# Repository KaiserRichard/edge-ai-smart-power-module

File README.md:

# Edge AI Smart Power Module — V1A-Lite

This branch (`feat/v1a-lite-cost-reduction`) captures **V1A-Lite option 1R**: 18–26 V normal auxiliary input (24 V nominal) → reverse protection and latched input cutoff → LM61460 → raw-node SCR crowbar → 7 A wiring fuse → Pi power output. The 100k/24.6k feedback divider sets 5.065 V nominal; 5 A operation remains a qualification target. Telemetry and the series shunt are removed.

**Phase D capture: ERC 0 errors / 0 warnings. Electrical release remains BLOCKED. NOT FOR FABRICATION — ENGINEERING REVIEW REQUIRED.** No Pi until dummy-load and OV/crowbar qualification gates pass.

Read the [Phase D capture and open items](docs/evidence/v1a_lite/PHASE_D_CAPTURE.md), [five-page schematic PDF](docs/schematic/V1A_Lite_schematic.pdf), [BOM](docs/evidence/v1a_lite/V1A_LITE_BOM.csv), and [progress/handoff](docs/evidence/v1a_lite/PHASE_D_PROGRESS.md). The schematic has root plus Sheets 01, 02, 03 and 05.

The old research design is preserved on **`v1a-research-schematic`** and **`v1a-research-layout-wip`**. The existing `V1A.kicad_pcb` is unchanged historical research layout, **not a V1A-Lite board**. Older context and architecture documents below describe research V1A unless explicitly identified as Lite; its 9–24 V/I2C architecture does not govern this branch. No final WBR battery or robot architecture is assumed.

## Start here

- [Current engineering state and blockers](docs/context/03_ENGINEERING_STATE.md)
- [Project overview](docs/context/01_PROJECT_OVERVIEW.md) and [current architecture](docs/context/02_V1A_ARCHITECTURE.md)
- [Workflow/gates](docs/context/05_WORKFLOW_AND_GATES.md), [decision index](docs/context/06_DECISION_LOG.md), and [learning sequence](docs/context/04_LEARNING_CURRICULUM.md)
- [Manager report](docs/FINAL_MANAGER_REPORT.md) and [detailed blocker evidence](docs/evidence/r2/forensic_2026-09-14/R2_R3_BLOCKER_REVIEW.md)
- [AI instructions](CLAUDE.md), [repository rules](AGENTS.md), and [Claude Project file selection](docs/CLAUDE_PROJECT_SETUP.md)

## Repository layout

| Path | Contents |
| --- | --- |
| `hardware/kicad/` | Lite root/four functional schematics and libraries; unchanged historical research PCB |
| `docs/context/` | Compact current project context; read before dated proposals |
| `docs/00_…05_*.md` | Requirements and design/review history; dated notices identify older state |
| `docs/evidence/` | Engineering provenance, calculations, contracts, source registers, dated netlists/ERC/review exports |
| `scripts/`, `tests/` | Calculation, capture, footprint, and repository checks |
| `software/power_monitor/` | Documented future telemetry work; no runtime implementation yet |
| `measurements/`, `fabrication/` | Documented future gated evidence/release areas |
| `third_party/` | Source registry, retained download manifest, small licensed historical reference extracts |

## Safe validation

From the repository root, with Python 3.11 or compatible Python 3:

```sh
python3 -B scripts/check_repository.py
python3 -B -m unittest discover -s tests -v
python3 -B scripts/check_v1a_lite.py
```

These commands check Lite capture integrity and retained historical regressions, not electrical release. The repository runner selects the Lite profile; incompatible research architecture suites are explicitly skipped. No software build is currently required. [Validation instructions](docs/VALIDATION.md) include fresh KiCad export/ERC commands, expected failure symptoms, and optional tools. Do not run the schematic builder as a check: it writes design files.

Vendor downloads, full predecessor repositories, backups, environments, and scratch renders were preserved in a sibling local archive. They are not restored by cloning GitHub. [Third-party policy/restoration](third_party/README.md) and the [cleanup record](docs/REPOSITORY_CLEANUP.md) explain dependencies and recovery. Historical engineering evidence remains in Git.

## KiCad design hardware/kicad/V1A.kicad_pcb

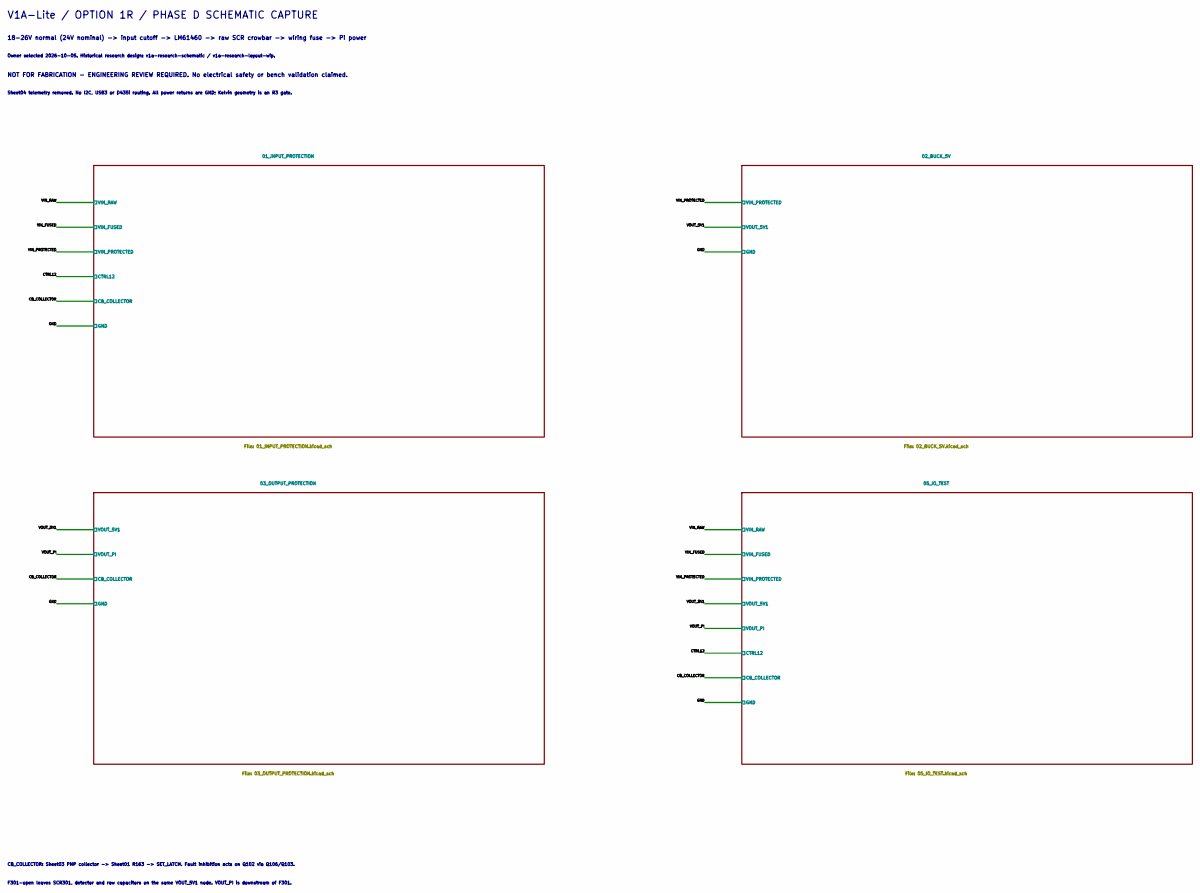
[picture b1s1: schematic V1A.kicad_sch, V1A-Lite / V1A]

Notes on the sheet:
V1A-Lite / OPTION 1R / PHASE D SCHEMATIC CAPTURE
18-26V normal (24V nominal) -> input cutoff -> LM61460 -> raw SCR crowbar -> wiring fuse -> Pi power
Owner selected 2026-10-05. Historical research design: v1a-research-schematic / v1a-research-layout-wip.
NOT FOR FABRICATION - ENGINEERING REVIEW REQUIRED. No electrical safety or bench validation claimed.
Sheet04 telemetry removed. No I2C, USB3 or D435i routing. All power returns are GND; Kelvin geometry is an R3 gate.
CB_COLLECTOR: Sheet03 PNP collector -> Sheet01 R163 -> SET_LATCH. Fault inhibition acts on Q102 via Q106/Q103.
F301-open leaves SCR301, detector and raw capacitors on the same VOUT_5V1 node. VOUT_PI is downstream of F301.

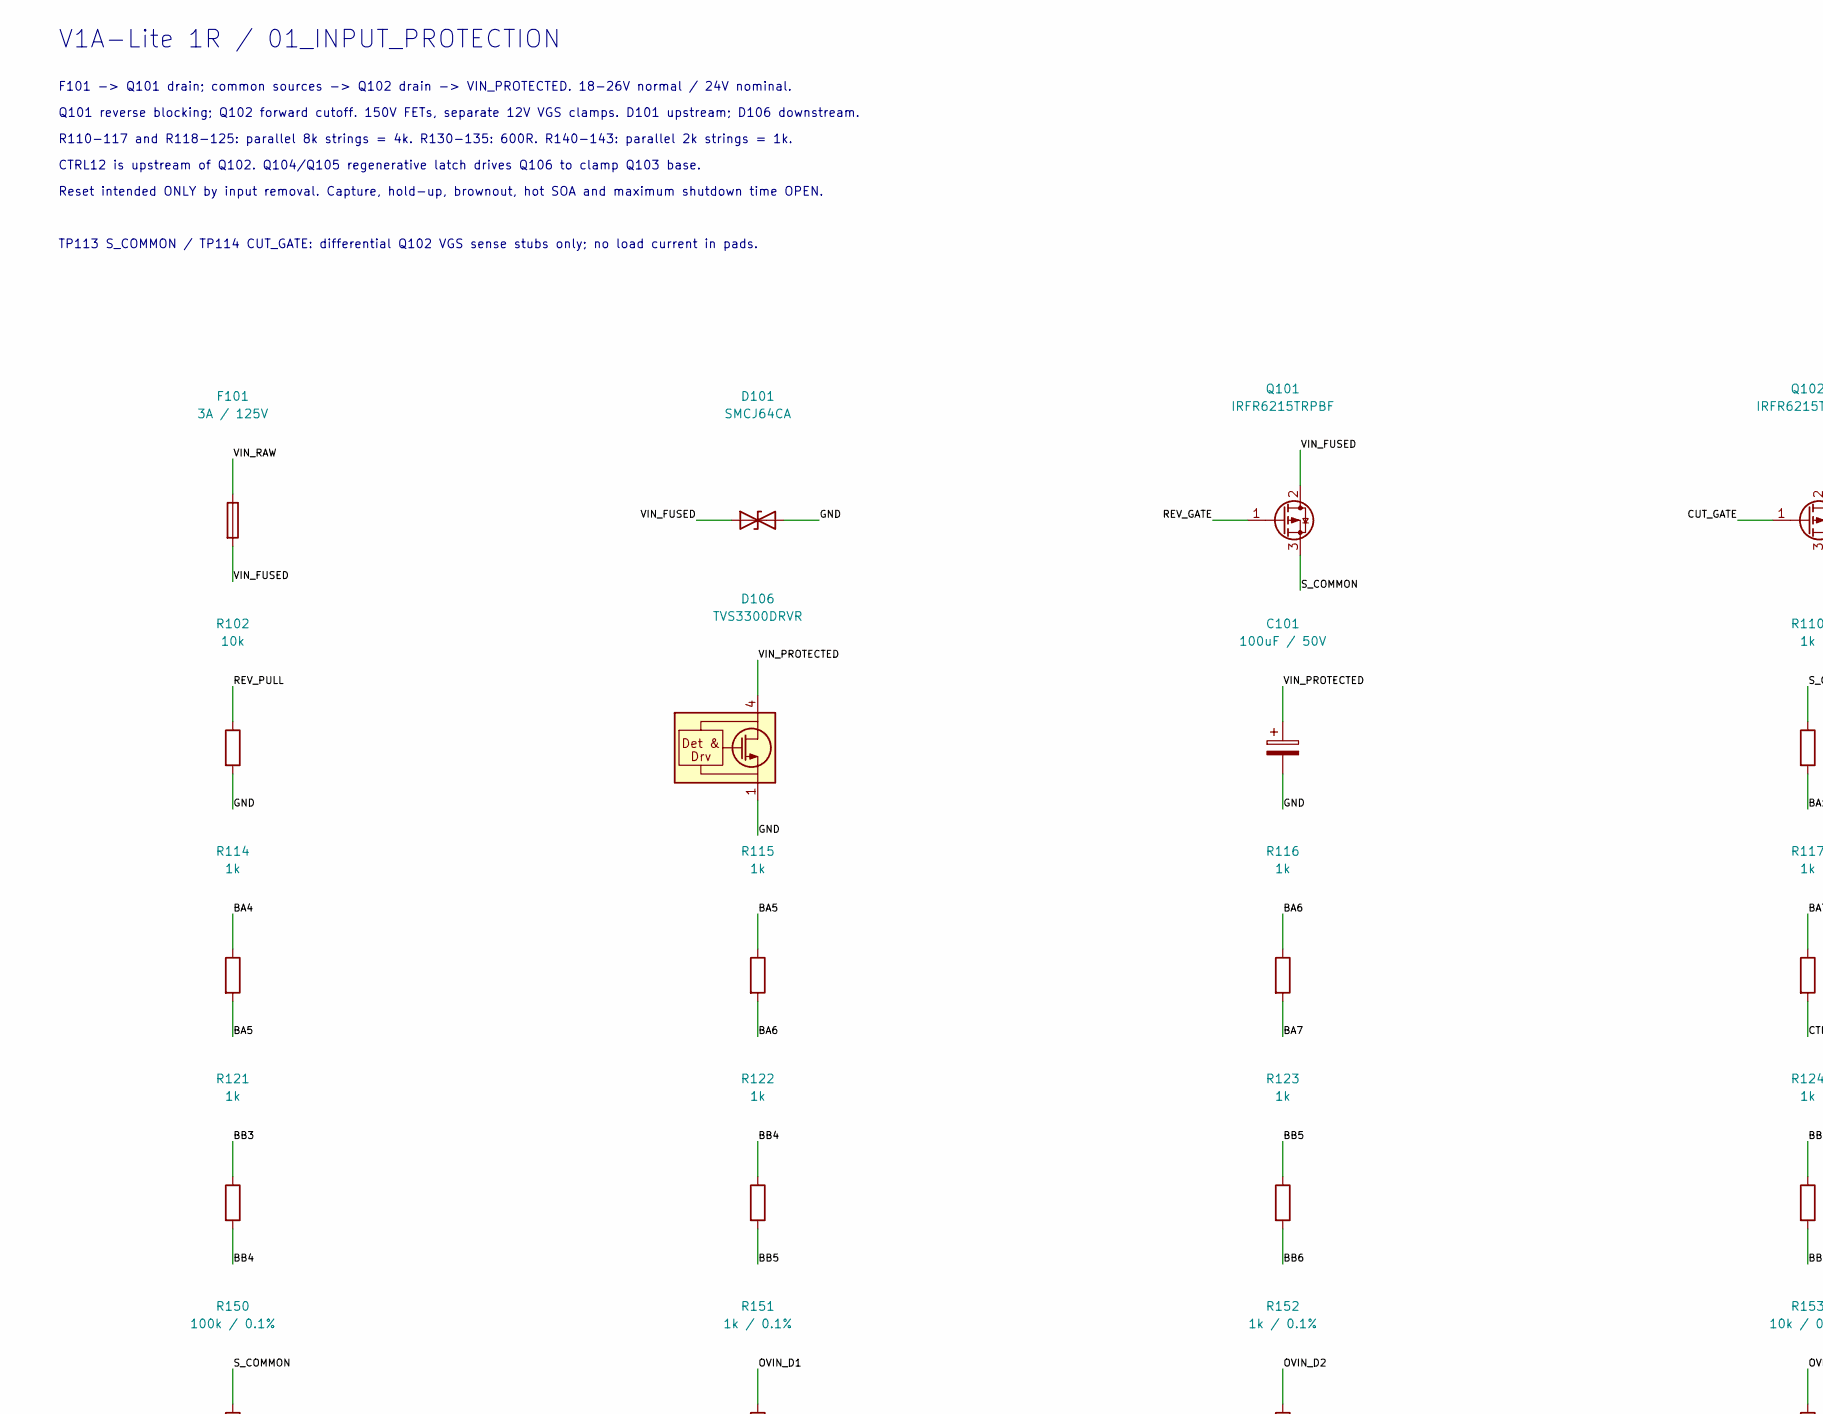
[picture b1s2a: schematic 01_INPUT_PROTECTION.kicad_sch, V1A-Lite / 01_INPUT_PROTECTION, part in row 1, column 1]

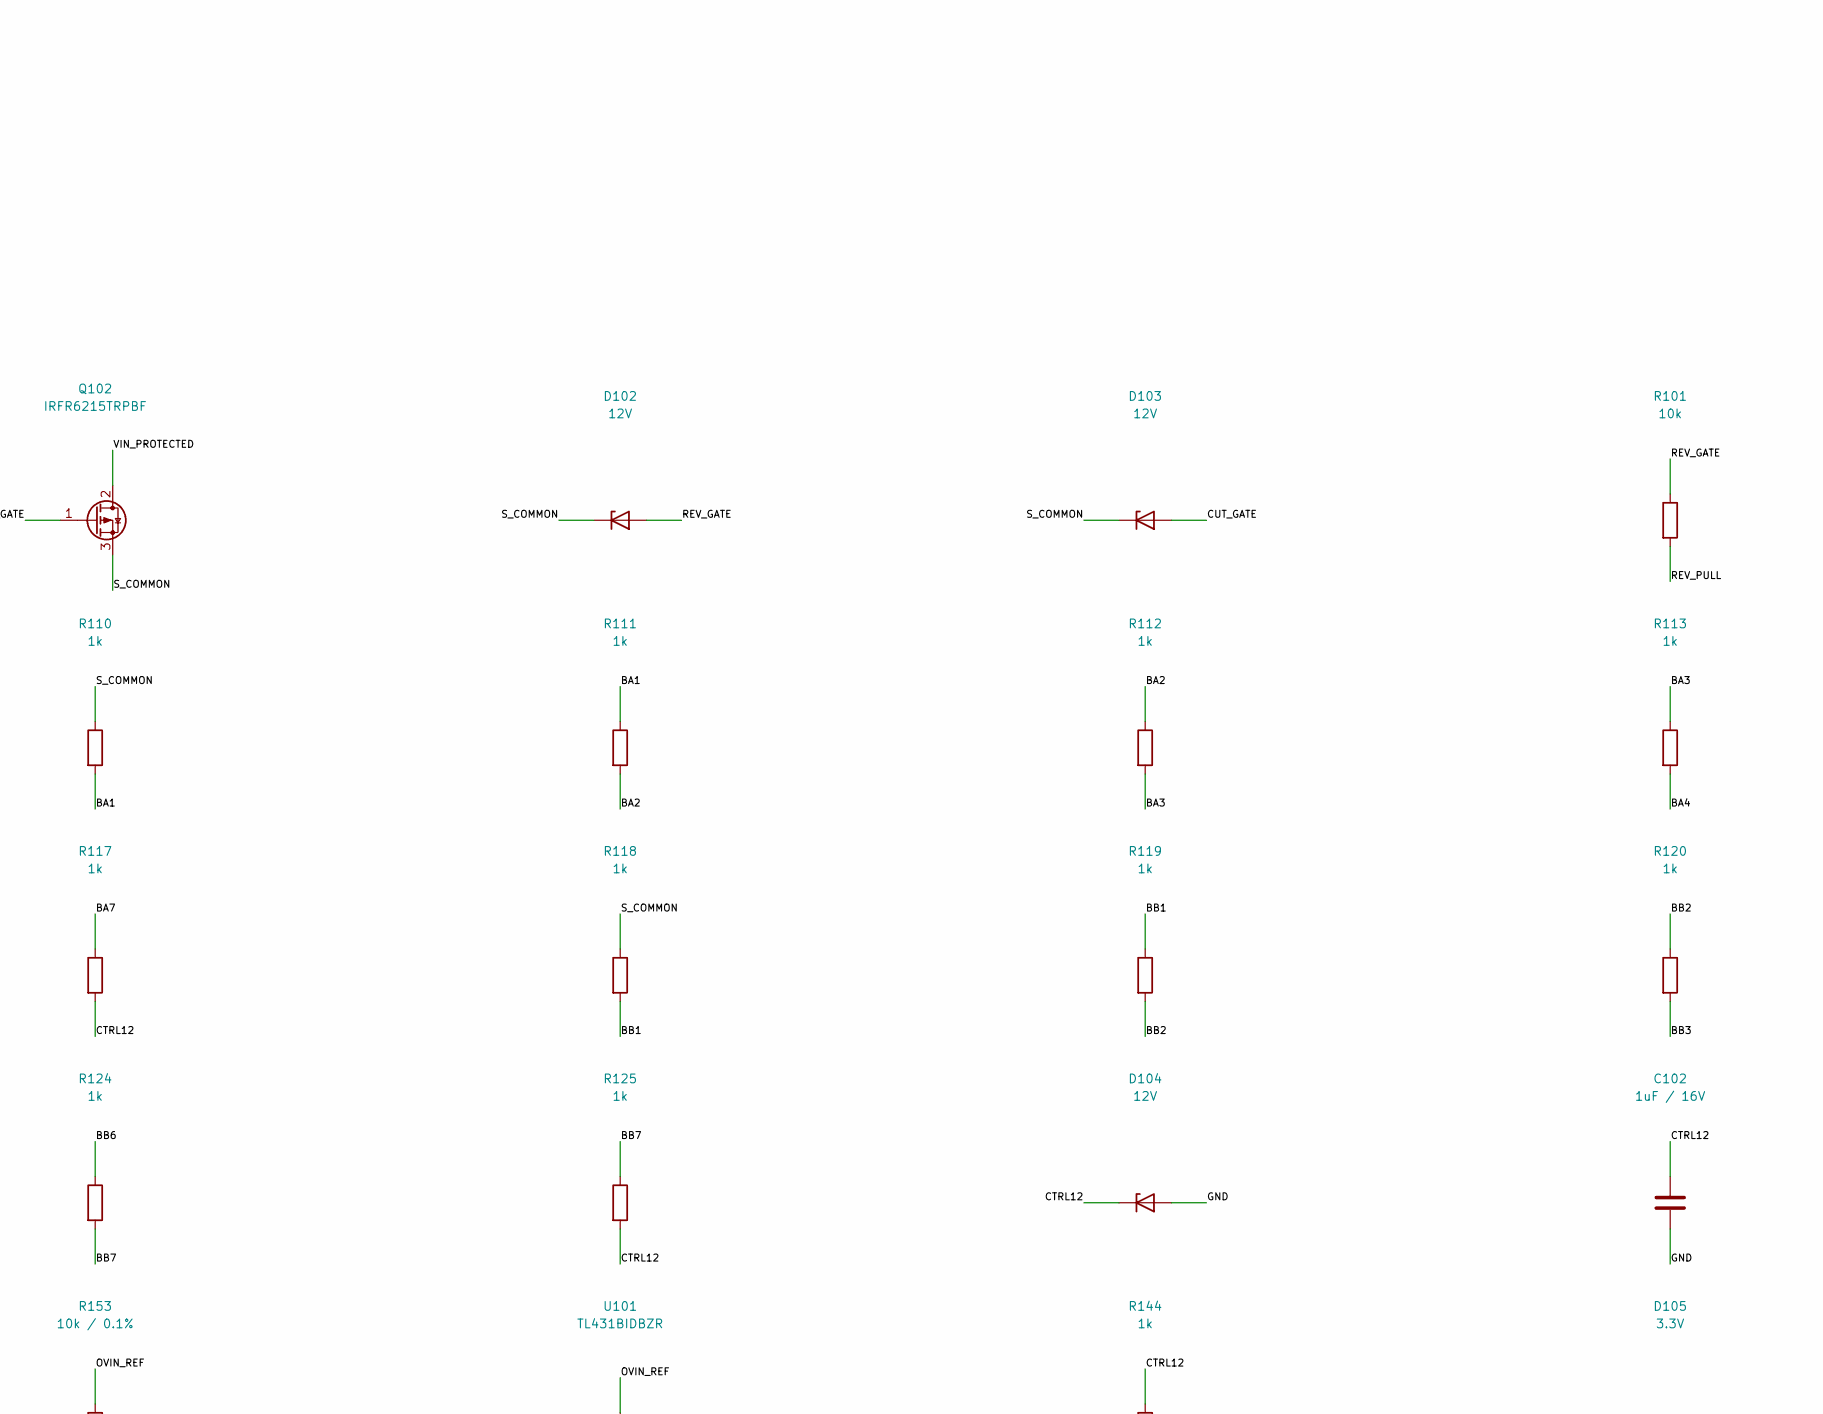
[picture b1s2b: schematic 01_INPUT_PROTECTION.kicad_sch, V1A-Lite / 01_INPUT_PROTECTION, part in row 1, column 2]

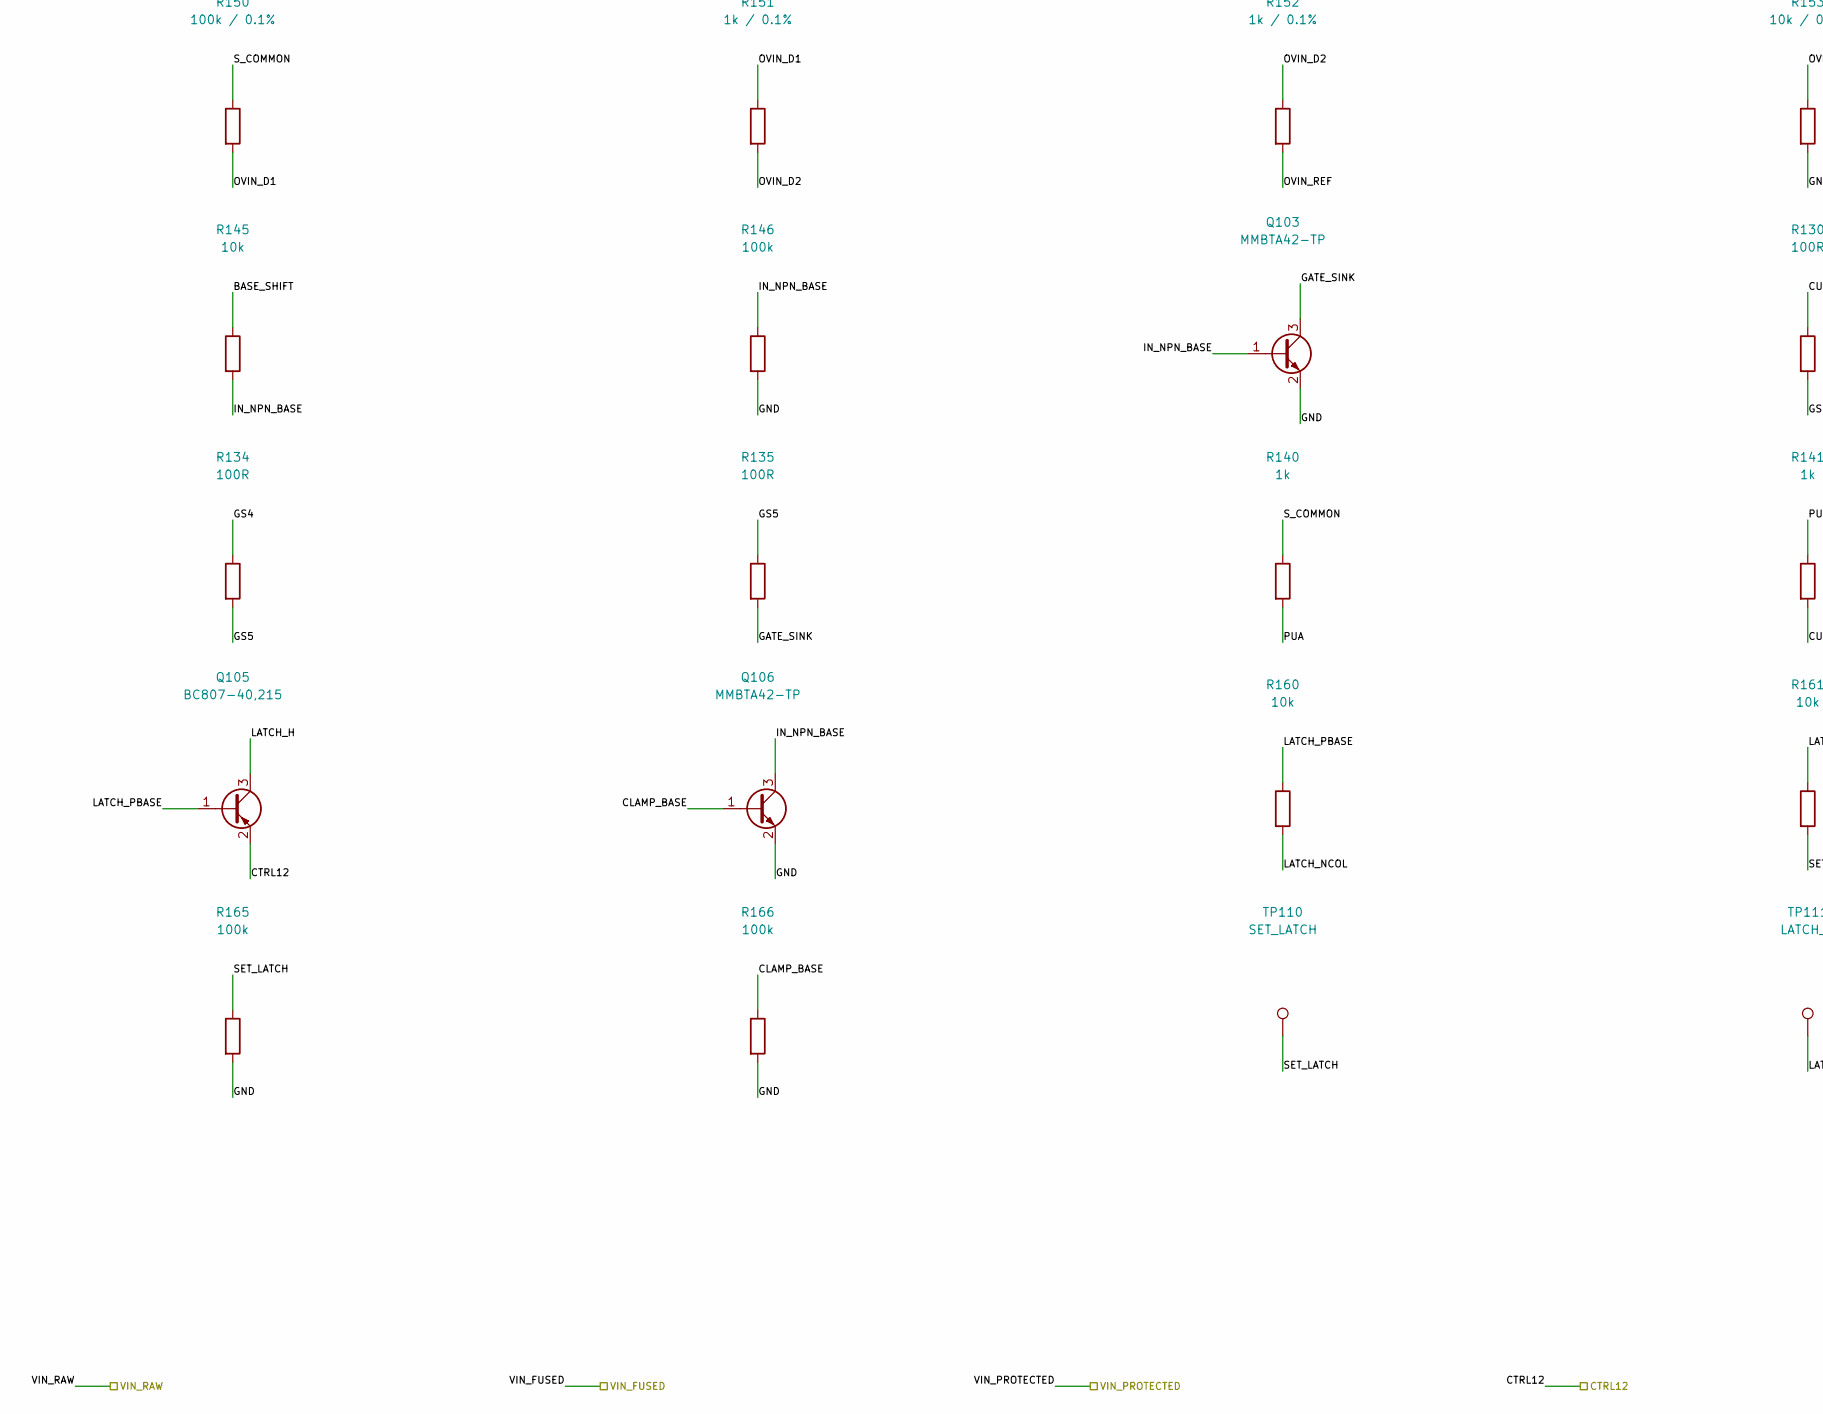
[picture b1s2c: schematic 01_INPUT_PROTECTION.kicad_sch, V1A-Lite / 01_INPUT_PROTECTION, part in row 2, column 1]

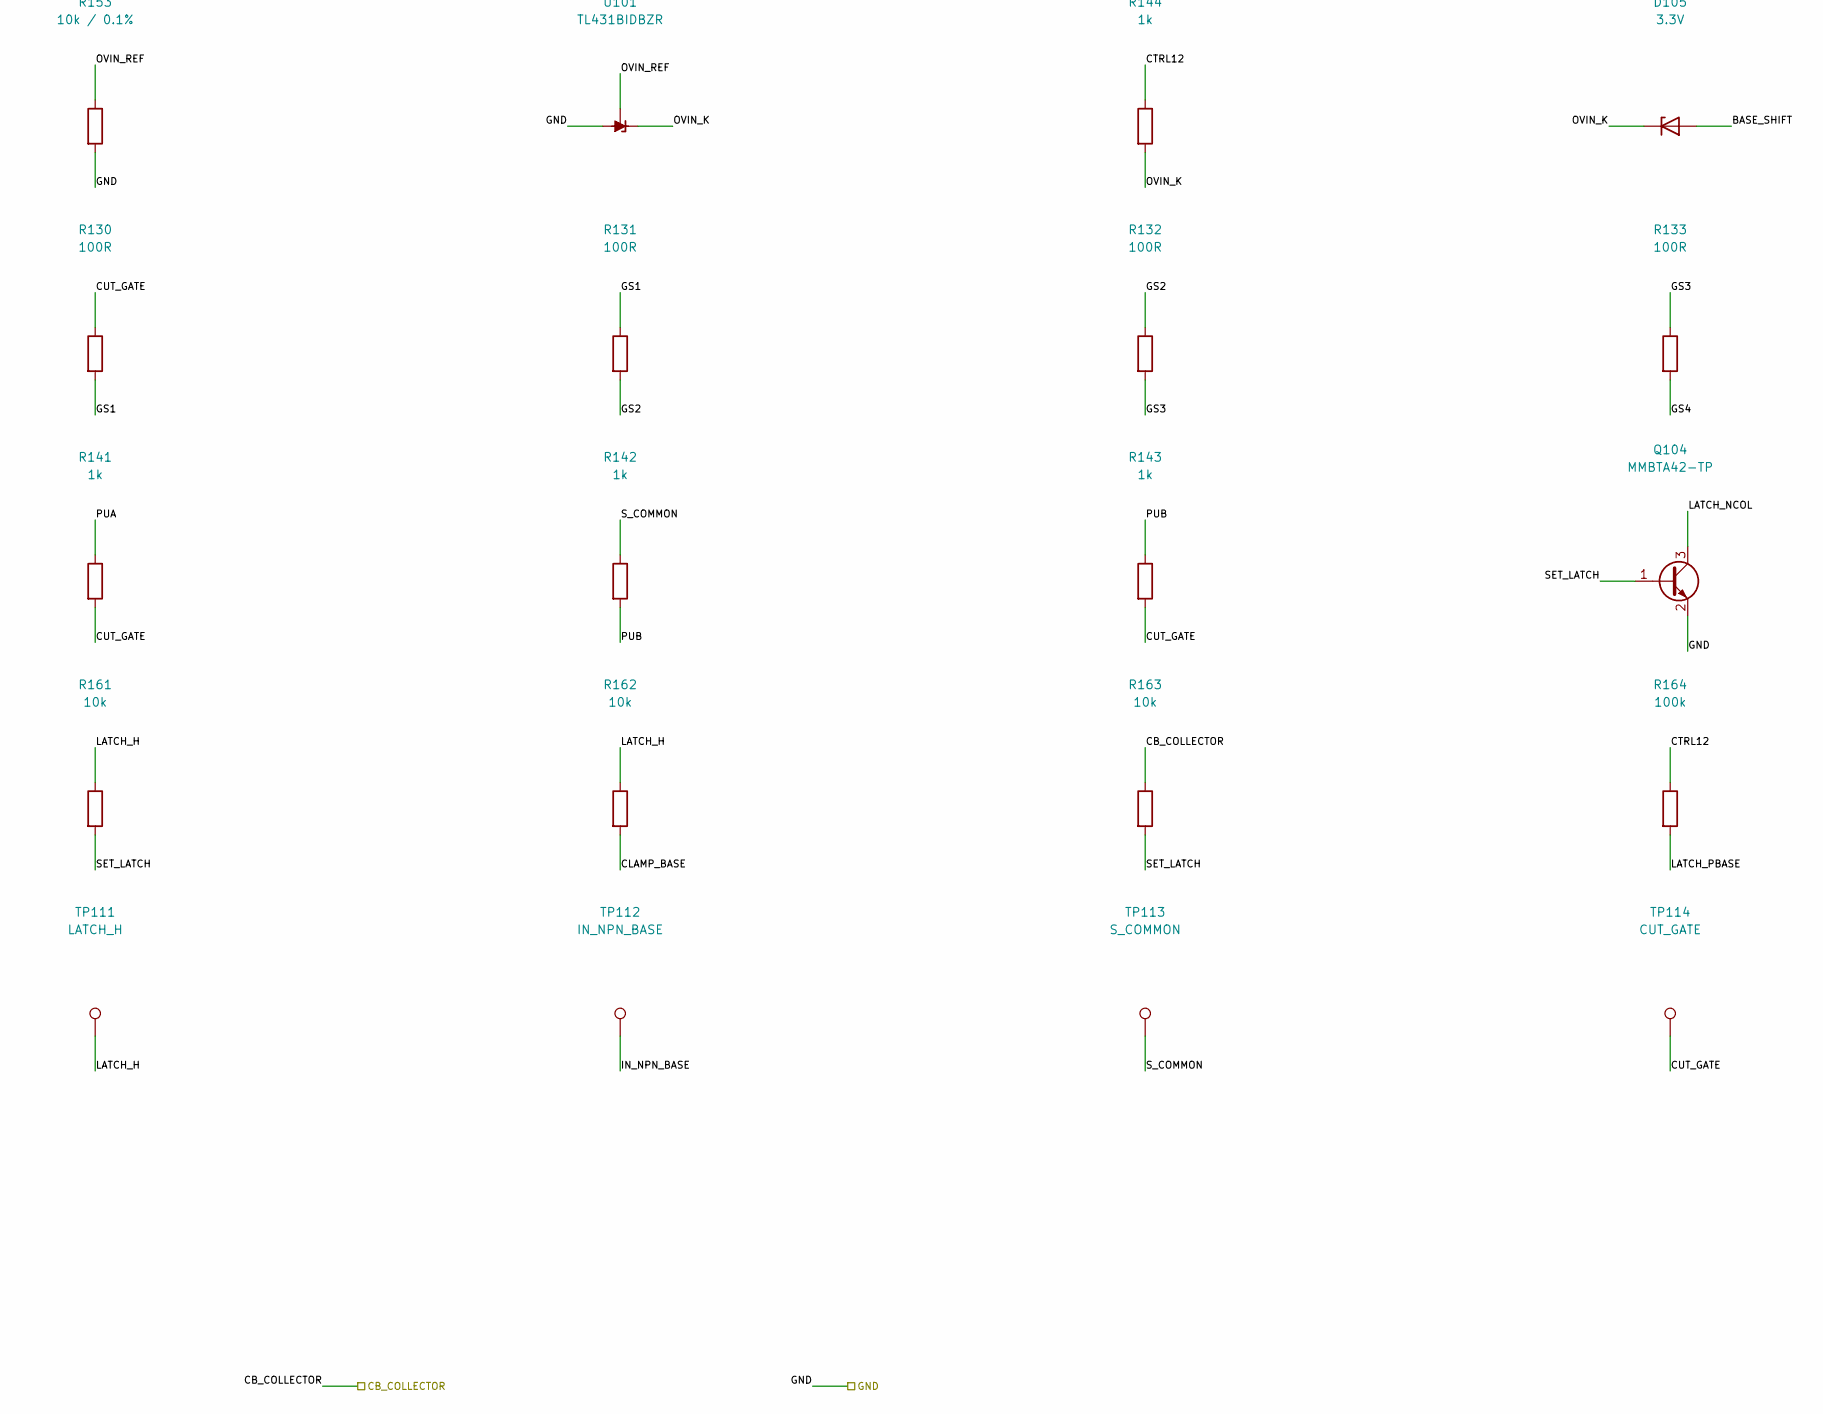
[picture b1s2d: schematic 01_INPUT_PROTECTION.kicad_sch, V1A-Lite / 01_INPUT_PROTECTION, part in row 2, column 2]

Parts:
C101: 100uF / 50V; CP_Radial_D8.0mm_P3.50mm; MPN EEUFR1H101; LCSC C178702
C102: 1uF / 16V; C_0805_2012Metric; MPN GRM21BR71C105KA01L; LCSC C77079
D101: SMCJ64CA; D_SMC; MPN SMCJ64CA; LCSC N/A - Mouser sourced
D102, D103, D104: 12V; D_SOD-123; MPN BZT52C12-7-F; LCSC C124196
D105: 3.3V; D_SOD-123; MPN BZT52C3V3-7-F; LCSC C151564
D106: TVS3300DRVR; DFN-6-1EP_2x2mm_P0.65mm_EP1x1.6mm; MPN TVS3300DRVR; LCSC C2863624
F101: 3A / 125V; Fuse_Littelfuse-NANO2-451_453; MPN 0451003.MRL; LCSC C13982
Q101, Q102: IRFR6215TRPBF; TO-252-2; MPN IRFR6215TRPBF; LCSC C150936
Q103, Q104, Q106: MMBTA42-TP; SOT-23; MPN MMBTA42-TP; LCSC C78715
Q105: BC807-40,215; SOT-23; MPN BC807-40,215; LCSC C57316
R101, R102, R145, R160, R161, R162, R163: 10k; R_0805_2012Metric; MPN 0805W8F1002T5E; LCSC C17414
R110, R111, R112, R113, R114, R115, R116, R117, R118, R119, R120, R121, R122, R123, R124, R125, R140, R141, R142, R143, R144: 1k; R_0603_1608Metric; MPN 0603WAF1001T5E; LCSC C21190
R130, R131, R132, R133, R134, R135: 100R; R_0603_1608Metric; MPN 0603WAF1000T5E; LCSC C22775
R146, R164, R165, R166: 100k; R_0603_1608Metric; MPN 0603WAF1003T5E; LCSC C25803
R150: 100k / 0.1%; R_0603_1608Metric; MPN TNPW0603100KBEEA; LCSC C844888
R151, R152: 1k / 0.1%; R_0603_1608Metric; MPN RT0603BRD071KL; LCSC C110776
R153: 10k / 0.1%; R_0603_1608Metric; MPN TNPW060310K0BEEA; LCSC C844890
TP110: SET_LATCH; TestPoint_Pad_D2.0mm; MPN PCB_FEATURE; LCSC N/A
TP111: LATCH_H; TestPoint_Pad_D2.0mm; MPN PCB_FEATURE; LCSC N/A
TP112: IN_NPN_BASE; TestPoint_Pad_D2.0mm; MPN PCB_FEATURE; LCSC N/A
TP113: S_COMMON; TestPoint_Pad_D2.0mm; MPN PCB_FEATURE; LCSC N/A
TP114: CUT_GATE; TestPoint_Pad_D2.0mm; MPN PCB_FEATURE; LCSC N/A
U101: TL431BIDBZR; SOT-23; MPN TL431BIDBZR; LCSC C41283

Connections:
/01_INPUT_PROTECTION/BA1: R110.2, R111.1
/01_INPUT_PROTECTION/BA2: R111.2, R112.1
/01_INPUT_PROTECTION/BA3: R112.2, R113.1
/01_INPUT_PROTECTION/BA4: R113.2, R114.1
/01_INPUT_PROTECTION/BA5: R114.2, R115.1
/01_INPUT_PROTECTION/BA6: R115.2, R116.1
/01_INPUT_PROTECTION/BA7: R116.2, R117.1
/01_INPUT_PROTECTION/BASE_SHIFT: D105.2 (A), R145.1
/01_INPUT_PROTECTION/BB1: R118.2, R119.1
/01_INPUT_PROTECTION/BB2: R119.2, R120.1
/01_INPUT_PROTECTION/BB3: R120.2, R121.1
/01_INPUT_PROTECTION/BB4: R121.2, R122.1
/01_INPUT_PROTECTION/BB5: R122.2, R123.1
/01_INPUT_PROTECTION/BB6: R123.2, R124.1
/01_INPUT_PROTECTION/BB7: R124.2, R125.1
/01_INPUT_PROTECTION/CLAMP_BASE: Q106.1 (B), R162.2, R166.1
/01_INPUT_PROTECTION/CUT_GATE: D103.2 (A), Q102.1 (G), R130.1, R141.2, R143.2, TP114.1
/01_INPUT_PROTECTION/GATE_SINK: Q103.3 (C), R135.2
/01_INPUT_PROTECTION/GS1: R130.2, R131.1
/01_INPUT_PROTECTION/GS2: R131.2, R132.1
/01_INPUT_PROTECTION/GS3: R132.2, R133.1
/01_INPUT_PROTECTION/GS4: R133.2, R134.1
/01_INPUT_PROTECTION/GS5: R134.2, R135.1
/01_INPUT_PROTECTION/IN_NPN_BASE: Q103.1 (B), Q106.3 (C), R145.2, R146.1, TP112.1
/01_INPUT_PROTECTION/LATCH_H: Q105.3 (C), R161.1, R162.1, TP111.1
/01_INPUT_PROTECTION/LATCH_NCOL: Q104.3 (C), R160.2
/01_INPUT_PROTECTION/LATCH_PBASE: Q105.1 (B), R160.1, R164.2
/01_INPUT_PROTECTION/OVIN_D1: R150.2, R151.1
/01_INPUT_PROTECTION/OVIN_D2: R151.2, R152.1
/01_INPUT_PROTECTION/OVIN_K: D105.1 (K), R144.2, U101.1 (K)
/01_INPUT_PROTECTION/OVIN_REF: R152.2, R153.1, U101.2 (REF)
/01_INPUT_PROTECTION/PUA: R140.2, R141.1
/01_INPUT_PROTECTION/PUB: R142.2, R143.1
/01_INPUT_PROTECTION/REV_GATE: D102.2 (A), Q101.1 (G), R101.1
/01_INPUT_PROTECTION/REV_PULL: R101.2, R102.1
/01_INPUT_PROTECTION/SET_LATCH: Q104.1 (B), R161.2, R163.2, R165.1, TP110.1
/01_INPUT_PROTECTION/S_COMMON: D102.1 (K), D103.1 (K), Q101.3 (S), Q102.3 (S), R110.1, R118.1, R140.1, R142.1, R150.1, TP113.1
/CB_COLLECTOR: R163.1; also elsewhere on the board
/CTRL12: C102.1, D104.1 (K), Q105.2 (E), R117.2, R125.2, R144.1, R164.1; also elsewhere on the board
/GND: C101.2, C102.2, D101.2 (A2), D104.2 (A), D106.1 (GND), D106.2 (GND), D106.3 (GND), D106.7 (GND), Q103.2 (E), Q104.2 (E), Q106.2 (E), R102.2, R146.2, R153.2, R165.2, R166.2, U101.3 (A); also elsewhere on the board
/VIN_FUSED: D101.1 (A1), F101.2, Q101.2 (D); also elsewhere on the board
/VIN_PROTECTED: C101.1, D106.4 (IN), D106.5 (IN), D106.6 (IN), Q102.2 (D); also elsewhere on the board
/VIN_RAW: F101.1; also elsewhere on the board

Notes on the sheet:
V1A-Lite 1R / 01_INPUT_PROTECTION
F101 -> Q101 drain; common sources -> Q102 drain -> VIN_PROTECTED. 18-26V normal / 24V nominal.
Q101 reverse blocking; Q102 forward cutoff. 150V FETs, separate 12V VGS clamps. D101 upstream; D106 downstream.
R110-117 and R118-125: parallel 8k strings = 4k. R130-135: 600R. R140-143: parallel 2k strings = 1k.
CTRL12 is upstream of Q102. Q104/Q105 regenerative latch drives Q106 to clamp Q103 base.
Reset intended ONLY by input removal. Capture, hold-up, brownout, hot SOA and maximum shutdown time OPEN.
TP113 S_COMMON / TP114 CUT_GATE: differential Q102 VGS sense stubs only; no load current in pads.

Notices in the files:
parts and their libraries:
JST B2P-VH-FB-B(LF)(SN); eVH.pdf metadata2026-01-09 pp1-4; pitch3.96 drill1.70 boss1.45; mate VHR-2N plus SVH-21T-P1.1; adapted unchanged geometry from KiCad f64dbd7 CC-BY-SA-4.0 with design exception; KiCad library contributors
